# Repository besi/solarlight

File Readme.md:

# Solar Light
A smart, solar powered light that lights up in various colors.

# Parts
The following parts are used in the project.

| Identifier  | Description | 
| ------------- | ------------- |
| [Microcontroller][]  | Wemos D1 Mini |
| [Battery][] | 18650 Lipo Battery with holder |
| [Charger][] | TP4056 Lipo Charger  |
| [Solar Panel][] | 110x60mm Solar Panel  |
| [Voltage Regulator][] | MCP1700-3302E  |
| [Neopixels][] | Neopixel WS2812b  |
| LED | Status LED  |
| Resistor | Resistor for LED Value? |
| Capacitor | Value? |

[Neopixels]: https://www.bastelgarage.ch/5m-ws2812b-60led-m-led-neopixel-strip-rolle
[Solar Panel]: https://www.bastelgarage.ch/solarzelle-5v-200ma-1w-110x60mm?search=solar%20panel
[Charger]: https://www.bastelgarage.ch/tp4056-lithium-lipo-akku-batterie-lademodul-micro-usb-5v-1a
[Battery]: https://www.bastelgarage.ch/li-ion-akku-3000ma-18650-mit-schutzelektronik-und-stecker?search=schutzelektronik
[Microcontroller]: https://www.reichelt.de/de/de/d1-mini-esp8266-v2-0-d1-mini-p253978.html?r=1
[Voltage Regulator]:https://www.digikey.ch/de/products/detail/microchip-technology/MCP1700-3302E-TO/652680

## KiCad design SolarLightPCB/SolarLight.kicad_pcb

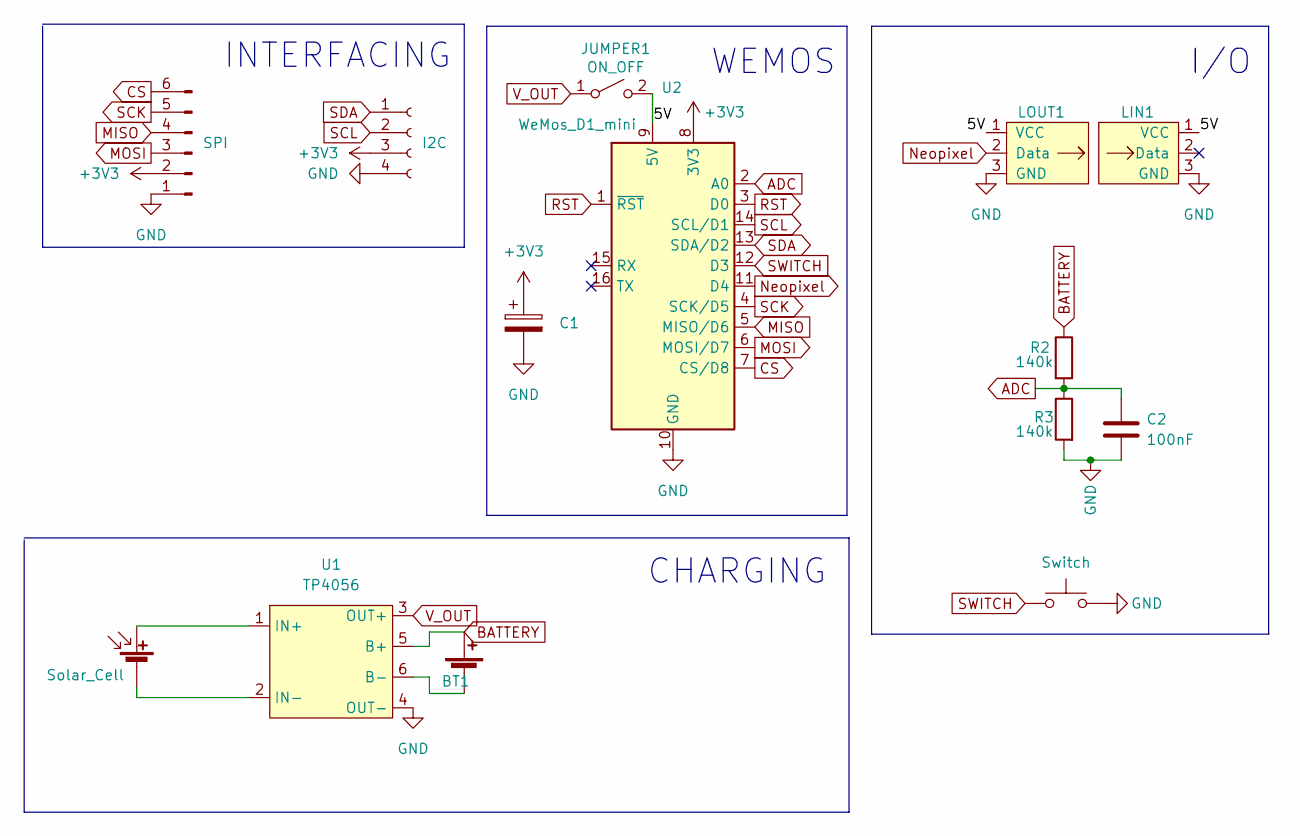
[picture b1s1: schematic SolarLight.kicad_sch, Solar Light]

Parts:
BT1: Battery_Cell; TerminalBlock_Phoenix_PT-1,5-2-3.5-H_1x02_P3.50mm_Horizontal
C1: C_Polarized; CP_Radial_D5.0mm_P2.50mm
C2: 100nF; C_Disc_D5.0mm_W2.5mm_P5.00mm
J1: I2C; PinHeader_1x04_P2.54mm_Vertical
J2: SPI; PinHeader_1x06_P2.54mm_Vertical
JUMPER1: ON_OFF; PinHeader_1x03_P2.54mm_Vertical
LIN1: LEDs_In; LED-Strip
LOUT1: LEDs_Out; LED-Strip
R2, R3: 140k; R_Axial_DIN0207_L6.3mm_D2.5mm_P7.62mm_Horizontal
SC1: Solar_Cell; TerminalBlock_Phoenix_PT-1,5-2-3.5-H_1x02_P3.50mm_Horizontal
SW1: Switch; SW_PUSH_6mm_H4.3mm
U1: TP4056
U2: WeMos_D1_mini; WEMOS_D1_mini_light

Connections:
+3V3: C1.1, J1.3, J2.2, U2.8 (3V3)
/5V: JUMPER1.2 (B), LIN1.1 (VCC), LOUT1.1 (VCC), U2.9 (5V)
ADC: C2.1, R2.2, R3.1, U2.2 (A0)
BATTERY: BT1.1 (+), R2.1, U1.5 (B+)
CS: J2.6, U2.7 (CS/D8)
GND: C1.2, C2.2, J1.4, J2.1, LIN1.3 (GND), LOUT1.3 (GND), R3.2, SW1.2, U1.4 (OUT-), U2.10 (GND)
MISO: J2.4, U2.5 (MISO/D6)
MOSI: J2.3, U2.6 (MOSI/D7)
Neopixel: LOUT1.2 (Data), U2.11 (D4)
unnamed: BT1.2 (-), U1.6 (B-)
unnamed: SC1.1 (+), U1.1 (IN+)
unnamed: SC1.2 (-), U1.2 (IN-)
RST: U2.1 (~RST), U2.3 (D0)
SCK: J2.5, U2.4 (SCK/D5)
SCL: J1.2, U2.14 (SCL/D1)
SDA: J1.1, U2.13 (SDA/D2)
SWITCH: SW1.1, U2.12 (D3)
V_OUT: JUMPER1.1 (A), U1.3 (OUT+)

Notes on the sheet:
INTERFACING
CHARGING
WEMOS
I/O

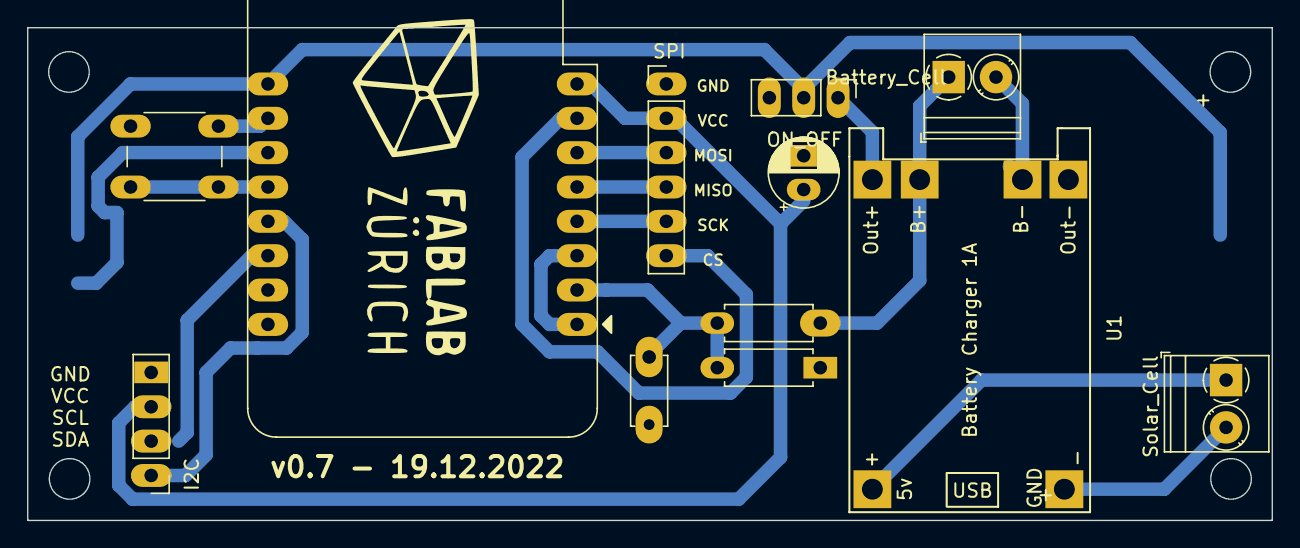
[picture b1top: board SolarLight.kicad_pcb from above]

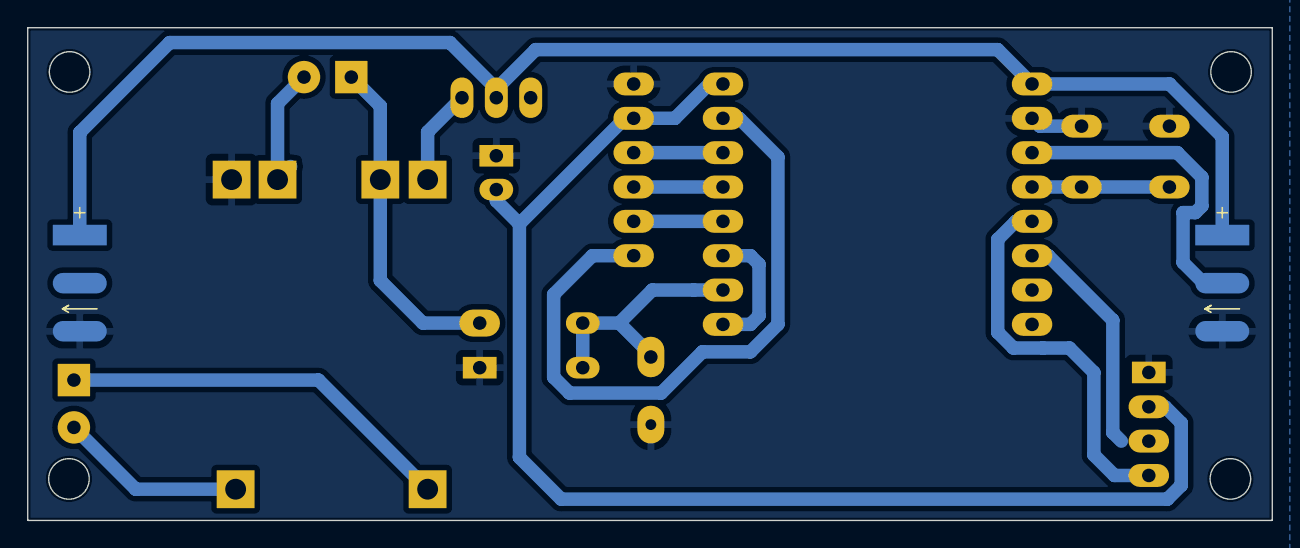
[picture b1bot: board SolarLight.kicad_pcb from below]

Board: 2 copper layers, 92.0 x 36.4 mm, 14 parts (2 on the bottom side), 18 nets.

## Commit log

2022-10-23 Add the list of parts
2022-10-23 Fix title of neopixel
2022-10-23 Added images
2022-10-23 Add git modules for libraries
    fixes #3
2022-10-23 Add PCB
2022-10-23 Replace the missing connection with a jumper
2022-10-23 Add missing trace
2022-10-23 Update schematic
2022-10-23 Add voltage divider to measure the battery voltage
    fixes #4
2022-10-23 Add a power on Jumper
    fixes #5
2022-10-23 Minor changes to PCB
    - Added _draft_ mounting holes
    - Added SPI and I2C labels
    - Changed the Board dimension to 100x45mm
2022-10-23 Update the pitch of the neopixel strips
2022-10-23 PCB Improvements
    - Bigger Package for the voltage regulator
    - Only one trace per pad (prefer to merge in the track instead)
    - Specify some minimal trace distance
    - Finer grid for the PCB to allow for better routing (5mils)
    - Cleanup unconnected traces
    - Ignore non-relevant DRC warnings
2022-10-23 Add the output of the neopixel pin to GND
    For now not the 3.3V since it’s hard to route that one over there
2022-10-24 Fix wrong pin numbering on the 3.3 voltage regulator
2022-10-24 PCB Improvements
    - Remove the LED
    - Make the pads biggger
    - Add a GND Plane
    - Add a logo
    - Connect both GND and VCC pads of the mechanical neopixel pin
    - Align positive / negative pins of Battery and solar panel
2022-10-24 Move the SPI header
2022-10-24 Untrack some items
2022-10-24 Cleanup some traces
2022-10-25 Add rotary encoder
2022-11-03 Add GND Jumper
2022-11-09 Make a “simplified” version
2022-11-17 Updated the simple pcb
2022-11-17 Remove the voltage regulator
2022-11-17 Reduce board size
2022-11-17 Add capacitor for measuring the Battery voltage
2022-11-17 Remove unused pads
2022-11-17 Add 1mm tracks
2022-11-18 Move the I2C and ON-OFF jumper closer to the edge
2022-11-18 Add the missing capacitor to the schema
    Fixing the warning because the pad of the charger module was removed
2022-11-18 Don’t commit rounded tracks
2022-11-20 Update silkscreen
2022-11-20 Added diode for reducing the voltage of the battery to ~3.3V
2022-11-20 Initial code
2022-12-19 Update TP4056 library
2022-12-19 Update gitmodules
2022-12-19 Use the 5V to 3V3 regulator of the Wemos D1
2022-12-21 Remove the resistor for measuring the battery voltage even in the disconnected state
